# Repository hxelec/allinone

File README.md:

KiCad files for BIG DECK all-in-one controller.
I would strongly recommend AGAINST going out and manufacturing this board because of the faulty reverse polarity protection circuit, which blocks reverse current, reducing reliability when the motors brake and try to return energy to the battery.
These files are only meant as a reference for people to learn from.
Thank you so much for your support :)
Ask me questions on the related video on my YouTube channel, I might not see them if you ask here on GitHub.

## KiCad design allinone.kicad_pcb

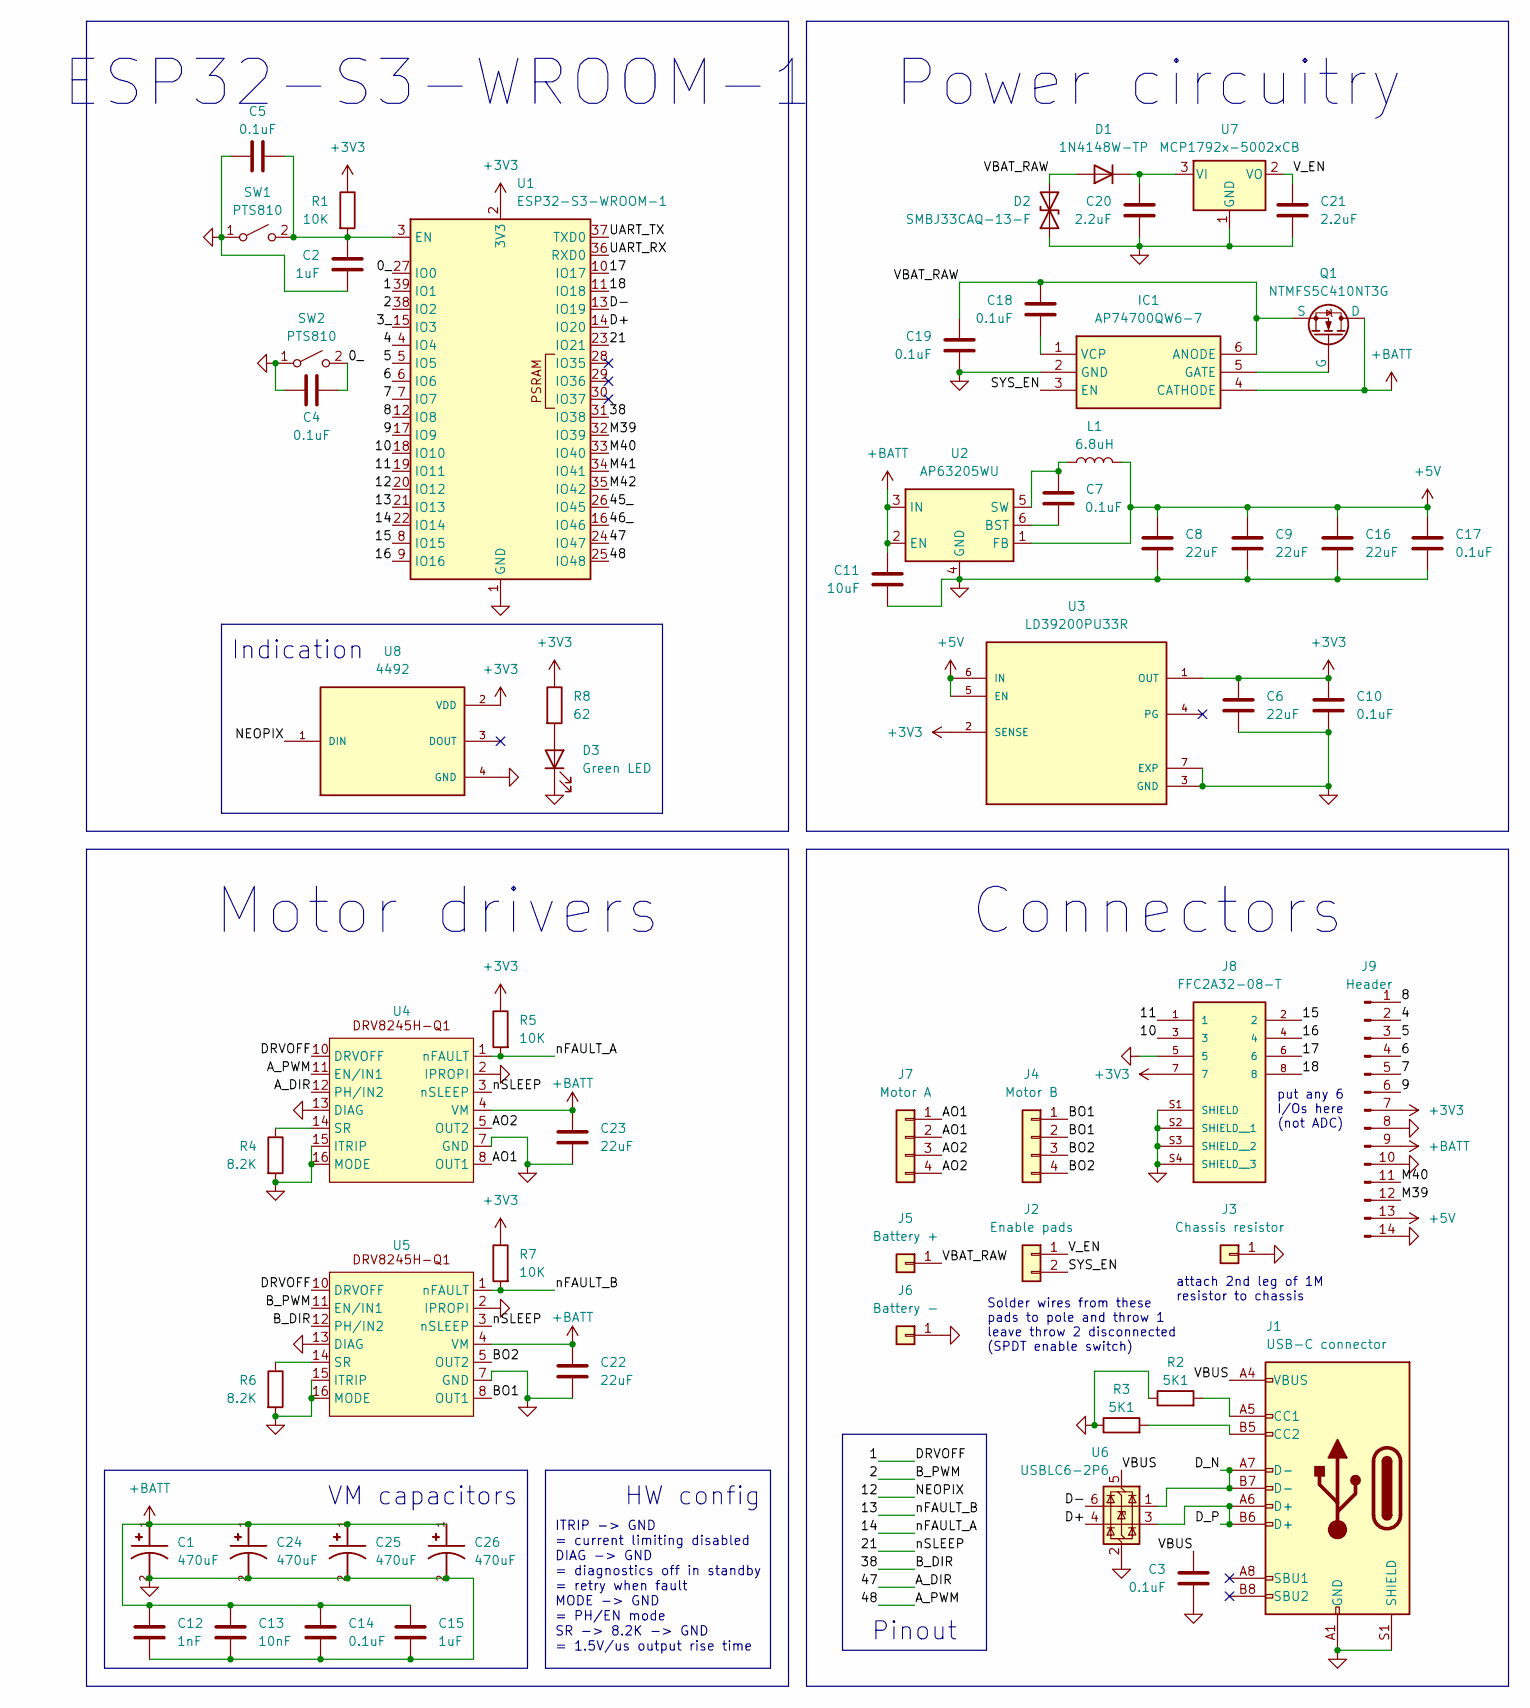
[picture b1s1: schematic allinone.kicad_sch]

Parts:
C1, C24, C25, C26: 470uF; CP_Radial_D8.0mm_P3.50mm; MPN EEU-FR1V471LB
C2, C15: 1uF; C_0402_1005Metric; MPN GRM155R6YA105KE11D
C3, C4, C5, C7, C10, C14, C17, C18, C19: 0.1uF; C_0402_1005Metric; MPN CGA2B3X7R1V104K050BB
C6, C8, C9, C16: 22uF; C_0603_1608Metric; MPN CL10A226MP8NUNE
C11: 10uF; C_0805_2012Metric; MPN GRM21BR6YA106ME43L
C12: 1nF; C_0402_1005Metric; MPN GRM1555C1H102JA01D
C13: 10nF; C_0402_1005Metric; MPN CGA2B3X7R1V103K050BB
C20, C21: 2.2uF; C_0603_1608Metric; MPN GRT188R61H225KE13D
C22, C23: 22uF; C_1206_3216Metric; MPN GMC31X5R226M35NT
D1: 1N4148W-TP; D_SOD-123; MPN 1N4148W-TP
D2: SMBJ33CAQ-13-F; D_SMB; MPN SMBJ33CAQ-13-F
D3: Green LED; LED_0805_2012Metric; MPN B1701UYG-20D000114U1930
IC1: AP74700QW6-7; SOT95P285X140-6N; MPN AP74700QW6-7
J1: USB-C connector; USB_C_Receptacle_GCT_USB4105-xx-A_16P_TopMnt_Horizontal; MPN USB4105-GF-A
J2: Enable pads; PinHeader_1x02_P2.54mm_Vertical
J3: Chassis resistor; SolderWire-0.5sqmm_1x01_D0.9mm_OD2.1mm
J4: Motor B; Motor pads 10A
J5: Battery +; Battery pads 30A
J6: Battery -; Battery pads 30A
J7: Motor A; Motor pads 10A
J8: FFC2A32-08-T; GCT_FFC2A32-08-T; PARTREV 0.1
J9: Header; PinHeader_1x14_P2.54mm_Vertical
L1: 6.8uH; L_Bourns_SRN6045TA; MPN SRN6045TA-4R7M
Q1: NTMFS5C410NT3G; ONSemi_SO-8FL_488AA; MPN NTMFS5C410NT3G
R1, R5, R7: 10K; R_0402_1005Metric; MPN RC0402JR-0710KL
R2, R3: 5K1; R_0402_1005Metric; MPN RC0402FR-075K1L
R4, R6: 8.2K; R_0402_1005Metric; MPN RC0402FR-078K2L
R8: 62; R_0402_1005Metric; MPN RC0402JR-0762RL
SW1, SW2: PTS810; SW_SPST_PTS810; MPN PTS810 SJK 250 SMTR LFS
U1: ESP32-S3-WROOM-1; MPN ESP32-S3-WROOM-1-N16R8
U2: AP63205WU; TSOT-23-6; MPN AP63205WU-7
U3: LD39200PU33R; SON95P300X300X100-7N-D; MPN LD39200PU33R
U4, U5: DRV8245H-Q1; MPN DRV8245HQRXZRQ1
U6: USBLC6-2P6; SOT-666; MPN USBLC6-2P6
U7: MCP1792x-5002xCB; SOT-23; MPN MCP1792T-5002H/CB
U8: 4492; LED_4492; MPN 4492

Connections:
+3V3: C6.1, C10.1, J8.7, J9.7, R1.1, R5.1, R7.1, R8.1, U1.2 (3V3), U3.1 (OUT), U3.2 (SENSE), U8.2 (VDD)
+5V: C8.1, C9.1, C16.1, C17.2, J9.13, L1.2, U2.1 (FB), U3.5 (EN), U3.6 (IN)
+BATT: C1.1, C11.1, C12.2, C13.2, C14.2, C15.2, C22.1, C23.1, C24.1, C25.1, C26.1, IC1.4 (CATHODE), J9.9, Q1.5 (D), Q1.6 (D), U2.2 (EN), U2.3 (IN), U4.4 (VM), U5.4 (VM)
/0_: C4.2, SW2.2 (B), U1.27 (IO0)
/1: U1.39 (IO1), U4.10 (DRVOFF), U5.10 (DRVOFF)
/2: U1.38 (IO2), U5.11 (EN/IN1)
/3_: U1.15 (IO3)
/4: J9.2, U1.4 (IO4)
/5: J9.3, U1.5 (IO5)
/6: J9.4, U1.6 (IO6)
/7: J9.5, U1.7 (IO7)
/8: J9.1, U1.12 (IO8)
/9: J9.6, U1.17 (IO9)
/10: J8.3, U1.18 (IO10)
/11: J8.1, U1.19 (IO11)
/12: U1.20 (IO12), U8.1 (DIN)
/13: R7.2, U1.21 (IO13), U5.1 (nFAULT)
/14: R5.2, U1.22 (IO14), U4.1 (nFAULT)
/15: J8.2, U1.8 (IO15)
/16: J8.4, U1.9 (IO16)
/17: J8.6, U1.10 (IO17)
/18: J8.8, U1.11 (IO18)
/21: U1.23 (IO21), U4.3 (nSLEEP), U5.3 (nSLEEP)
/38: U1.31 (IO38), U5.12 (PH/IN2)
/45_: U1.26 (IO45)
/46_: U1.16 (IO46)
/47: U1.24 (IO47), U4.12 (PH/IN2)
/48: U1.25 (IO48), U4.11 (EN/IN1)
/AO1: J7.1, J7.2, U4.8 (OUT1), U4.9 (OUT1)
/AO2: J7.3, J7.4, U4.5 (OUT2), U4.6 (OUT2)
/BO1: J4.1, J4.2, U5.8 (OUT1), U5.9 (OUT1)
/BO2: J4.3, J4.4, U5.5 (OUT2), U5.6 (OUT2)
/D+: U1.14 (IO20), U6.4 (I/O2)
/D-: U1.13 (IO19), U6.6 (I/O1)
/D_N: J1.A7 (D-), J1.B7 (D-), U6.1 (I/O1)
/D_P: J1.A6 (D+), J1.B6 (D+), U6.3 (I/O2)
/M39: J9.12, U1.32 (IO39)
/M40: J9.11, U1.33 (IO40)
/M41: U1.34 (IO41)
/M42: U1.35 (IO42)
/SYS_EN: IC1.3 (EN), J2.2
/UART_RX: U1.36 (RXD0)
/UART_TX: U1.37 (TXD0)
/VBAT_RAW: C18.2, C19.2, D1.2 (A), D2.2 (A2), IC1.6 (ANODE), J5.1, Q1.1 (S), Q1.2 (S), Q1.3 (S)
/VBUS: C3.1, J1.A4 (VBUS), J1.A9 (VBUS), J1.B4 (VBUS), J1.B9 (VBUS), U6.5 (VBUS)
/V_EN: C21.2, J2.1, U7.2 (VO)
GND: C1.2, C2.2, C3.2, C4.1, C5.2, C6.2, C8.2, C9.2, C10.2, C11.2, C12.1, C13.1, C14.1, C15.1, C16.2, C17.1, C19.1, C20.1, C21.1, C22.2, C23.2, C24.2, C25.2, C26.2, D2.1 (A1), D3.1 (K), IC1.2 (GND), J1.A1 (GND), J1.A12 (GND), J1.B1 (GND), J1.B12 (GND), J1.S1 (SHIELD), J3.1, J6.1, J8.5, J8.S1 (SHIELD), J8.S2 (SHIELD__1), J8.S3 (SHIELD__2), J8.S4 (SHIELD__3), J9.8, J9.10, J9.14, R2.1, R3.1, R4.2, R6.2, SW1.1 (A), SW2.1 (A), U1.1 (GND), U1.40 (GND), U1.41 (GND), U2.4 (GND), U3.3 (GND), U3.7 (EXP), U4.2 (IPROPI), U4.7 (GND), U4.13 (DIAG), U4.15 (ITRIP), U4.16 (MODE), U5.2 (IPROPI), U5.7 (GND), U5.13 (DIAG), U5.15 (ITRIP), U5.16 (MODE), U6.2 (GND), U7.1 (GND), U8.4 (GND)
unnamed: C20.2, D1.1 (K), U7.3 (VI)
unnamed: D3.2 (A), R8.2
unnamed: IC1.5 (GATE), Q1.4 (G)
unnamed: C18.1, IC1.1 (VCP)
unnamed: J1.A5 (CC1), R2.2
unnamed: J1.B5 (CC2), R3.2
unnamed: C2.1, C5.1, R1.2, SW1.2 (B), U1.3 (EN)
unnamed: C7.1, U2.6 (BST)
unnamed: C7.2, L1.1, U2.5 (SW)
unnamed: R4.1, U4.14 (SR)
unnamed: R6.1, U5.14 (SR)

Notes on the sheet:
Indication
ITRIP -> GND = current limiting disabled DIAG -> GND = diagnostics off in standby = retry when fault MODE -> GND = PH/EN mode SR -> 8.2K -> GND = 1.5V/us output rise time
ESP32-S3-WROOM-1
Motor drivers
Power circuitry
Connectors
Solder wires from these pads to pole and throw 1 leave throw 2 disconnected (SPDT enable switch)
put any 6 I/Os here (not ADC)
VM capacitors
HW config
Pinout
attach 2nd leg of 1M resistor to chassis

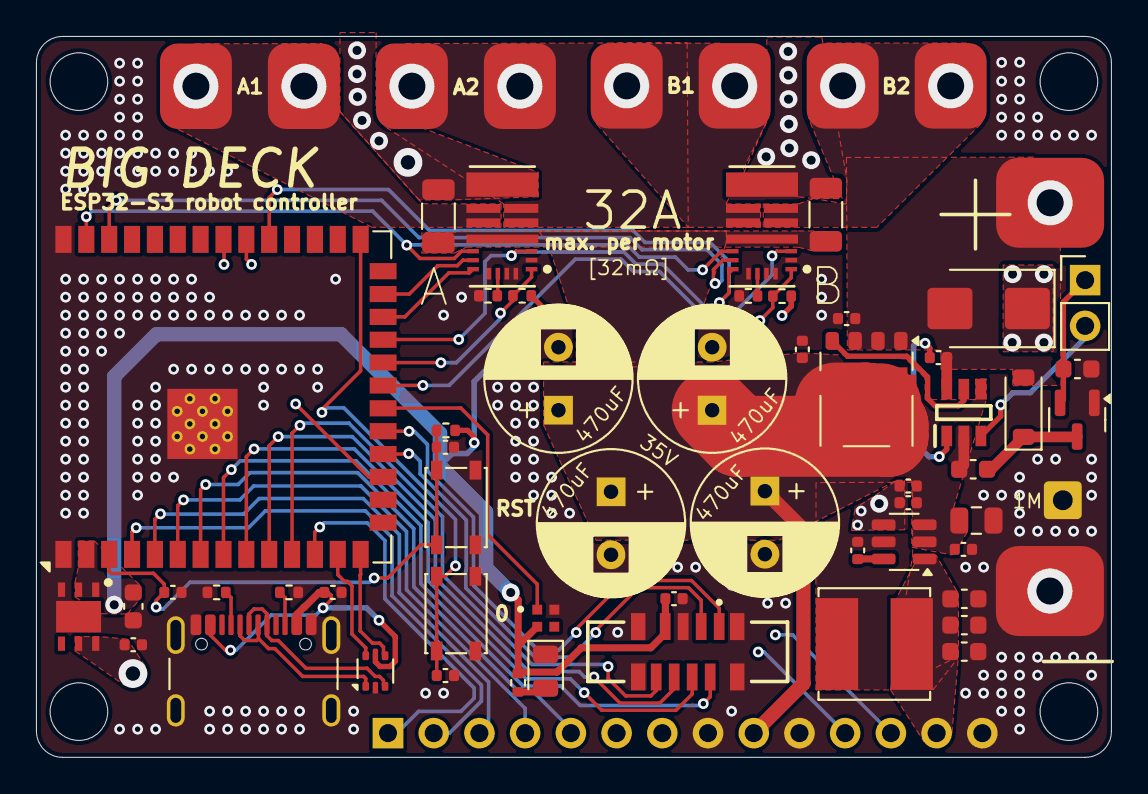
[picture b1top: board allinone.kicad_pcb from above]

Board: 4 copper layers, 59.7 x 40.0 mm, 59 parts (1 on the bottom side), 51 nets.
